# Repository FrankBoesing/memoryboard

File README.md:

# Memoryboard for Teensy 3.x

1..6x spi jedec-memory soic-8 (e.g. 23LC1024 RAM)

Partslist:

- 6 x SPI jedec Memory of your choice* (SOIC-8) (RAM (e.g. 23LC1024) , Flash...)
- 1 x 74LCX126MX SOIC-14
- 1 x 74LCX138MX SOIC-16
- 6 x Capacitor 0.1uF 0603
- 3 x Resistor 10K 0603

*Check package-width!

https://forum.pjrc.com/threads/29276-Limits-of-delay-effect-in-audio-library
(up to 9 sec. delay for audio 44kHz)

Of course, this board is not only for the audio-library! 

OSH-Park shared project:
https://oshpark.com/shared_projects/KZt5PaU7

Video of delay effect:

Pins used:
- 3v3, 
- GND, 
- 2,3,4 (Chipselects) 
- 7, 12, 14 (SPI)

### License

<br />This work is licensed under a <a rel="license" href="http://creativecommons.org/licenses/by-sa/4.0/">Creative Commons Attribution-ShareAlike 4.0 International License</a>.

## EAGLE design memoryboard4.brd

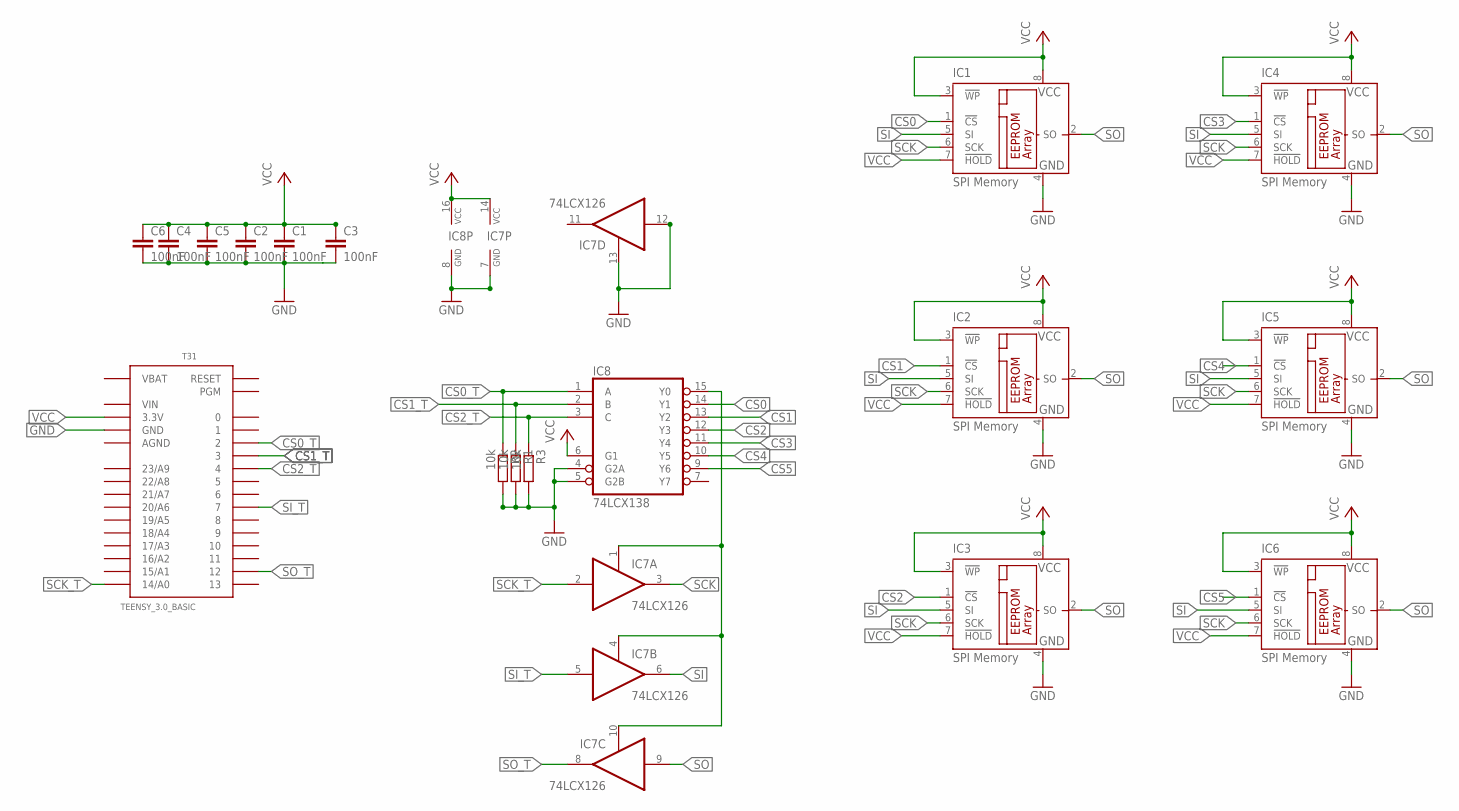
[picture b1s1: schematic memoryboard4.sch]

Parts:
C1, C2, C3, C4, C5, C6: 100nF; C0603
IC1, IC2, IC3, IC4, IC5, IC6: SPI Memory; SO-08
IC7: 74LCX126; SO14
IC8: 74LCX138; SO16
R1, R2, R3: 10k; R0603
T31: TEENSY_3.0_BASIC

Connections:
AGND: T31.AGND
CS0: IC1.1 (!CS), IC8.14 (Y1)
CS0_T: IC8.1 (A), R2.1, T31.2
CS1: IC2.1 (!CS), IC8.13 (Y2)
CS1_T: IC8.2 (B), R1.1, T31.3
CS2: IC3.1 (!CS), IC8.12 (Y3)
CS2_T: IC8.3 (C), R3.1, T31.4
CS3: IC4.1 (!CS), IC8.11 (Y4)
CS4: IC5.1 (!CS), IC8.10 (Y5)
CS5: IC6.1 (!CS), IC8.9 (Y6)
GND: C1.2, C2.2, C3.2, C4.2, C5.2, C6.2, IC1.4 (GND), IC2.4 (GND), IC3.4 (GND), IC4.4 (GND), IC5.4 (GND), IC6.4 (GND), IC7.7 (GND), IC7.12 (I), IC7.13 (OE), IC8.4 (G2A), IC8.5 (G2B), IC8.8 (GND), R1.2, R2.2, R3.2, T31.GND, T31.GND1 (GND)
SCK: IC1.6 (SCK), IC2.6 (SCK), IC3.6 (SCK), IC4.6 (SCK), IC5.6 (SCK), IC6.6 (SCK), IC7.3 (O)
SCK_T: IC7.2 (I), T31.14/A0
SI: IC1.5 (SI), IC2.5 (SI), IC3.5 (SI), IC4.5 (SI), IC5.5 (SI), IC6.5 (SI), IC7.6 (O)
SI_T: IC7.5 (I), T31.7
SO: IC1.2 (SO), IC2.2 (SO), IC3.2 (SO), IC4.2 (SO), IC5.2 (SO), IC6.2 (SO), IC7.9 (I)
SO_T: IC7.8 (O), T31.12
SPI_ENABLE: IC7.1 (OE), IC7.4 (OE), IC7.10 (OE), IC8.15 (Y0)
VBAT: T31.VBAT
VCC: C1.1, C2.1, C3.1, C4.1, C5.1, C6.1, IC1.3 (!WP), IC1.7 (!HOLD), IC1.8 (VCC), IC2.3 (!WP), IC2.7 (!HOLD), IC2.8 (VCC), IC3.3 (!WP), IC3.7 (!HOLD), IC3.8 (VCC), IC4.3 (!WP), IC4.7 (!HOLD), IC4.8 (VCC), IC5.3 (!WP), IC5.7 (!HOLD), IC5.8 (VCC), IC6.3 (!WP), IC6.7 (!HOLD), IC6.8 (VCC), IC7.14 (VCC), IC8.6 (G1), IC8.16 (VCC), T31.3.3V, T31.3.3V1 (3.3V)
VIN: T31.VIN

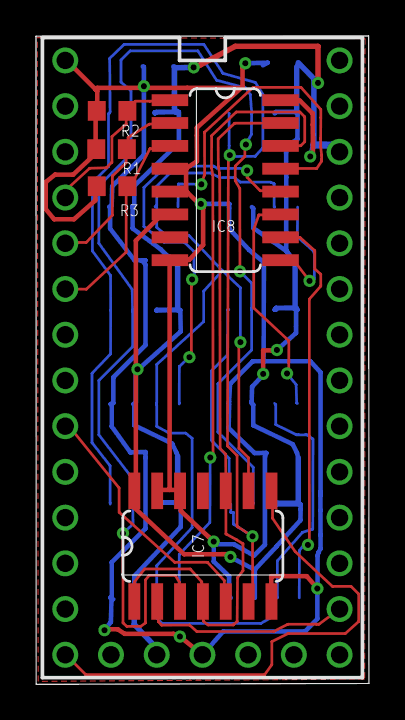
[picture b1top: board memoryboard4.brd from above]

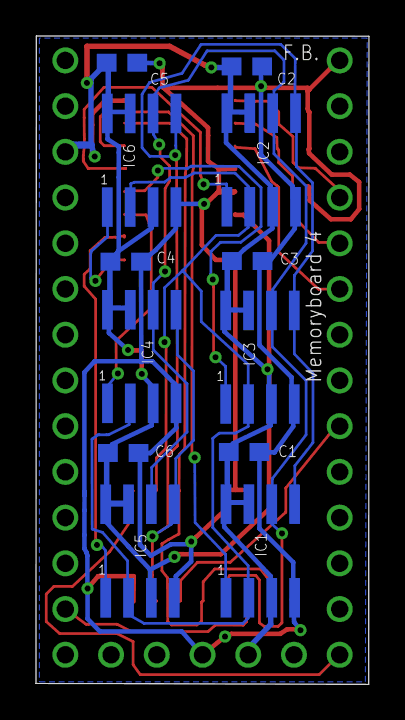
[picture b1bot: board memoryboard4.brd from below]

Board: 2 copper layers, 18.5 x 36.0 mm, 18 parts (12 on the bottom side), 18 nets.

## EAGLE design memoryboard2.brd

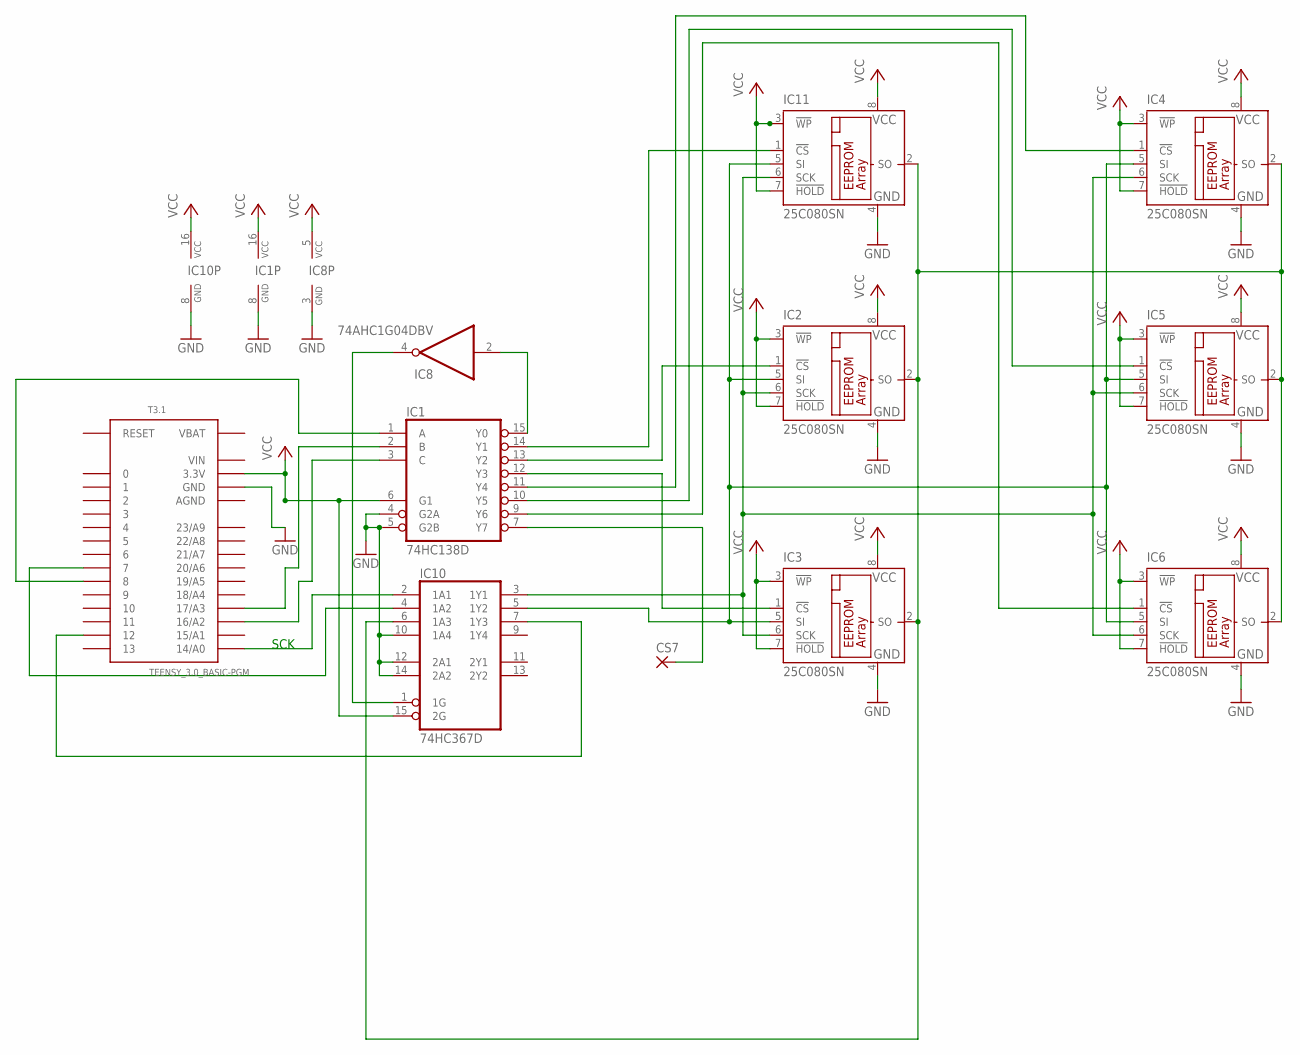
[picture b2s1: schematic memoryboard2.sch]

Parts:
CS7: SMD2; SMD1,27-2,54
IC1: 74HC138D; SO16
IC2, IC3, IC4, IC5, IC6, IC11: 25C080SN; SO-08
IC8: 74AHC1G04DBV; SOT23-5
IC10: 74HC367D; SO16
T3.1: TEENSY_3.0_BASIC-PGM

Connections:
AGND: T3.1.AGND
GND: IC1.4 (G2A), IC1.5 (G2B), IC1.8 (GND), IC2.4 (GND), IC3.4 (GND), IC4.4 (GND), IC5.4 (GND), IC6.4 (GND), IC8.3 (GND), IC10.8 (GND), IC10.10 (1A4), IC10.12 (2A1), IC10.14 (2A2), IC11.4 (GND), T3.1.GND, T3.1.GND1 (GND)
unnamed: IC8.4 (O), IC10.1 (1G)
unnamed: IC10.2 (1A1), T3.1.14/A0
unnamed: IC10.4 (1A2), T3.1.7
unnamed: IC10.7 (1Y3), T3.1.12
unnamed: IC1.15 (Y0), IC8.2 (I)
unnamed: IC1.3 (C), T3.1.16/A2
unnamed: CS7.1, IC1.7 (Y7)
unnamed: IC1.10 (Y5), IC5.1 (!CS)
unnamed: IC2.6 (SCK), IC3.6 (SCK), IC4.6 (SCK), IC5.6 (SCK), IC6.6 (SCK), IC10.3 (1Y1), IC11.6 (SCK)
unnamed: IC1.2 (B), T3.1.17/A3
unnamed: IC1.9 (Y6), IC6.1 (!CS)
unnamed: IC1.12 (Y3), IC3.1 (!CS)
unnamed: IC2.2 (SO), IC3.2 (SO), IC4.2 (SO), IC5.2 (SO), IC6.2 (SO), IC10.6 (1A3), IC11.2 (SO)
unnamed: IC1.11 (Y4), IC4.1 (!CS)
unnamed: IC1.1 (A), T3.1.8
unnamed: IC2.5 (SI), IC3.5 (SI), IC4.5 (SI), IC5.5 (SI), IC6.5 (SI), IC10.5 (1Y2), IC11.5 (SI)
unnamed: IC1.14 (Y1), IC11.1 (!CS)
unnamed: IC1.13 (Y2), IC2.1 (!CS)
VBAT: T3.1.VBAT
VCC: IC1.6 (G1), IC1.16 (VCC), IC2.3 (!WP), IC2.7 (!HOLD), IC2.8 (VCC), IC3.3 (!WP), IC3.7 (!HOLD), IC3.8 (VCC), IC4.3 (!WP), IC4.7 (!HOLD), IC4.8 (VCC), IC5.3 (!WP), IC5.7 (!HOLD), IC5.8 (VCC), IC6.3 (!WP), IC6.7 (!HOLD), IC6.8 (VCC), IC8.5 (VCC), IC10.15 (2G), IC10.16 (VCC), IC11.3 (!WP), IC11.7 (!HOLD), IC11.8 (VCC), T3.1.3.3V, T3.1.3.3V1 (3.3V)
VIN: T3.1.VIN

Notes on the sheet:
SCK

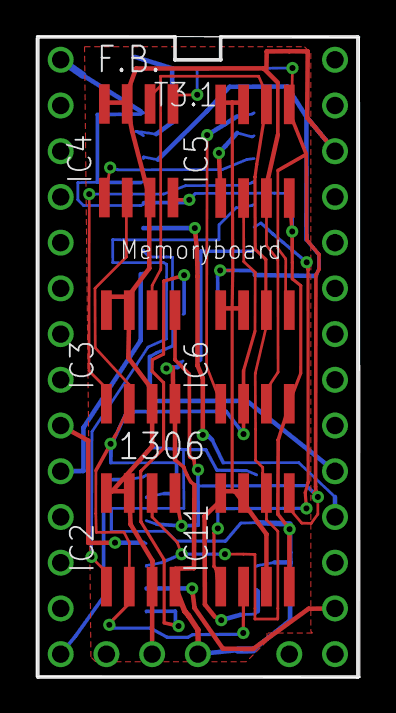
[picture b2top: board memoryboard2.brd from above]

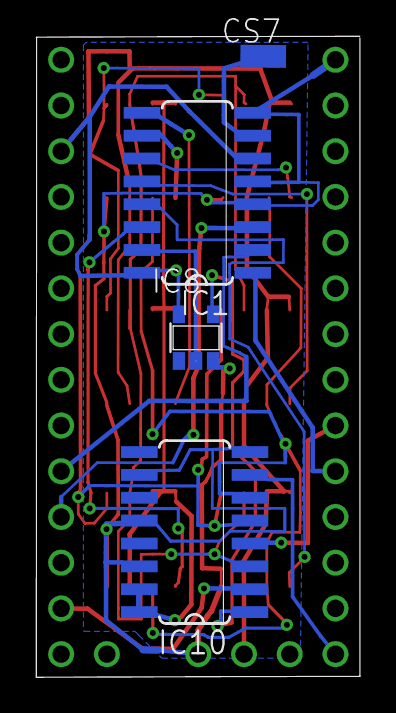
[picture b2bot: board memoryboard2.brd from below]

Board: 2 copper layers, 18.0 x 35.6 mm, 11 parts (4 on the bottom side), 20 nets.

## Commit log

2015-07-05 schematic png
2015-07-08 New Revision
2015-07-13 new revision, more capacitors, added led
2015-08-02 Add Testsoftware for RAMs
2015-08-19 Update "Memoryboard 4"
2015-08-19 move photos to /img
2015-09-06 improved DMA, rmv need of DmaSpi
2015-09-06 only 6
2015-09-06 macro magic
2016-04-21 Add CC-SA-4.0
